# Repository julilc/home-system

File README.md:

# HOME SYSTEM

Home System is an intelligent home automation project that combines an ESP32 device, MQTT messaging, a Python backend, a SQL Server database, and a conversational AI assistant. 

The system reads environmental data such as temperature, humidity, and luminosity, stores it persistently, exposes it through a FastAPI API, and lets the user interact through a React frontend. The assistant can answer questions about the home state and invoke tools to turn lights on/off, check sensor values, and report the current status of the environment.

---

## 1. OVERVIEW

This project integrates:
* ESP32 firmware for collecting sensor data
* MQTT broker communication for telemetry and actuator commands
* Python backend with FastAPI and AI tool-calling
* SQL Server database for persistence
* React + Vite frontend for user interaction
* KiCad electrical/electronic design files for the hardware
* AI agent layer using an external model API

---

## 2. MAIN FEATURES

* SENSOR MONITORING:
  - Temperature
  - Humidity
  - Luminosity
  - Light status

* DEVICE CONTROL:
  - LED on/off commands through MQTT

* CONVERSATIONAL INTERFACE:
  - Spanish assistant named Carlitos
  - Tool-based responses for home automation tasks

* PERSISTENT MEMORY:
  - User conversations and metadata stored in SQL Server

* WEB DASHBOARD:
  - React chat interface for interaction with the home system

* HARDWARE DOCUMENTATION:
  - KiCad schematics and PCB files

---

## 3. ARCHITECTURE

The system is organized in layers. In practice:
1. The ESP32 publishes sensor values to MQTT topics.
2. A Python listener consumes those messages and persists the values in the database.
3. The backend API receives chat requests from the frontend.
4. The assistant decides whether to answer directly or call a tool.
5. Tool calls can read the database or trigger MQTT commands to control the LED.

---

## 4. TECH STACK

* BACKEND: Python, FastAPI, Paho MQTT, pyodbc, pandas, dotenv, SQL Server
* FRONTEND: React, Vite, JavaScript / JSX
* EMBEDDED / HARDWARE: ESP32, DHT11 (temp/humidity), LDR (light), MQTT protocol, Arduino C++
* AI LAYER: OpenRouter API, Chat-completions model, Tool-calling architecture
* ELECTRONICS / PCB: KiCad for schematic and PCB design

---

## 5. ENVIRONMENT CONFIGURATION

This project uses environment variables stored in a `.env` file at the project root. 

IMPORTANT:
* Do not commit real secrets or API keys.
* The repository already includes a `.gitignore` to avoid pushing `.env` files.

---

## 6. DATABASE

The project uses Microsoft SQL Server and expects a database called `home`.

SQL Scripts:
* `database_config/create_database.sql`: Creates the database
* `database_config/create_tables_and_views.sql`: Creates the tables (Temperature, Humidity, Luminosity, LightStatus, MusicPlayed, PersonsRegistered, HomeStatus, LedStatus, Memories)

Database Access:
* Connection logic is defined in: `backend/database/sql/conection.py`
* Main queries and insert helpers: `backend/database/sql/insert.py` & `backend/database/sql/select.py`

---

## 7. BACKEND & API

The backend is built with FastAPI and is defined in: `backend/api_services/api.py`

Endpoints:
* `GET /api/health`: Returns service status
* `POST /api/chat`: Receives a user message, returns an AI response (using tool calling if needed), and persists the conversation.

---

## 8. AGENT AND TOOLS

The AI assistant uses:
* `agent/planning.py`: Defines the system prompt for the assistant.
* `agent/tools.json`: Describes the tool APIs exposed to the model.
* `backend/services/agent_services/tool_registry.py`: Registers actual Python functions behind each tool name.

Available tools: 
get_temperature, get_humidity, get_luminosity, get_home_status, get_light_status, get_music_played, get_persons_registered, turn_on_light, turn_off_light, play_music.

---

## 9. MQTT LISTENER

Implemented in: `backend/services/mqtt_services/mqtt_listener.py`
It subscribes to sensor topics (Temperature, Humidity, Luminosity, LED control, LED confirmation/status) and inserts the received values into the database.

---

## 10. FRONTEND

The frontend is a React app created with Vite located in the `frontend/` directory.
It displays chat messages, sends messages to the backend, shows server/ESP32 status, and provides quick action buttons.

---

## 11. FIRMWARE & HARDWARE BEHAVIOR

Located in `firmware/main/main.ino` (and related folders).

Hardware behavior:
* Connects to WiFi and MQTT broker.
* Publishes sensor data every 10 seconds (DHT11 temp/humidity, LDR luminosity).
* Detects sound events via an interrupt.
* Subscribes to LED control messages and publishes confirmation messages back to MQTT.

Pin mapping:
* DHT11: GPIO 23
* LDR: GPIO 34
* SOUND: GPIO 26
* LED: GPIO 27

---

## 12. DOCUMENTATION & TEST FILES

* HARDWARE DESIGN: `documentation/KiCad/` includes schematics, PCB layouts, footprints, and the ESP32 symbol library.
* TEST FILES: `test/sql/insert_memories.py` demonstrates how memory records can be inserted for validation.

---

## 13. DEVELOPMENT SETUP & USAGE

1. PYTHON BACKEND: Create a virtual environment, install requirements, and run the FastAPI server via uvicorn.
2. FRONTEND: Navigate to `frontend/`, run `npm install`, then `npm run dev`.
3. MQTT LISTENER: Run the MQTT Python script to start listening to the broker.
4. FIRMWARE: Open `firmware/main/main.ino` in Arduino IDE, select the ESP32 board, configure WiFi, and upload.

USAGE EXAMPLE:
Once everything is running, open the browser and chat with the assistant.
Try prompts like:
* “¿Cuál es la temperatura actual?”
* “¿Cómo está la humedad?”
* “Enciende la luz del dormitorio”

---

NOTES:
* This is an educational/prototype system.
* It relies on a real MQTT broker and SQL Server instance.
* API credentials must be kept private in the `.env` file.

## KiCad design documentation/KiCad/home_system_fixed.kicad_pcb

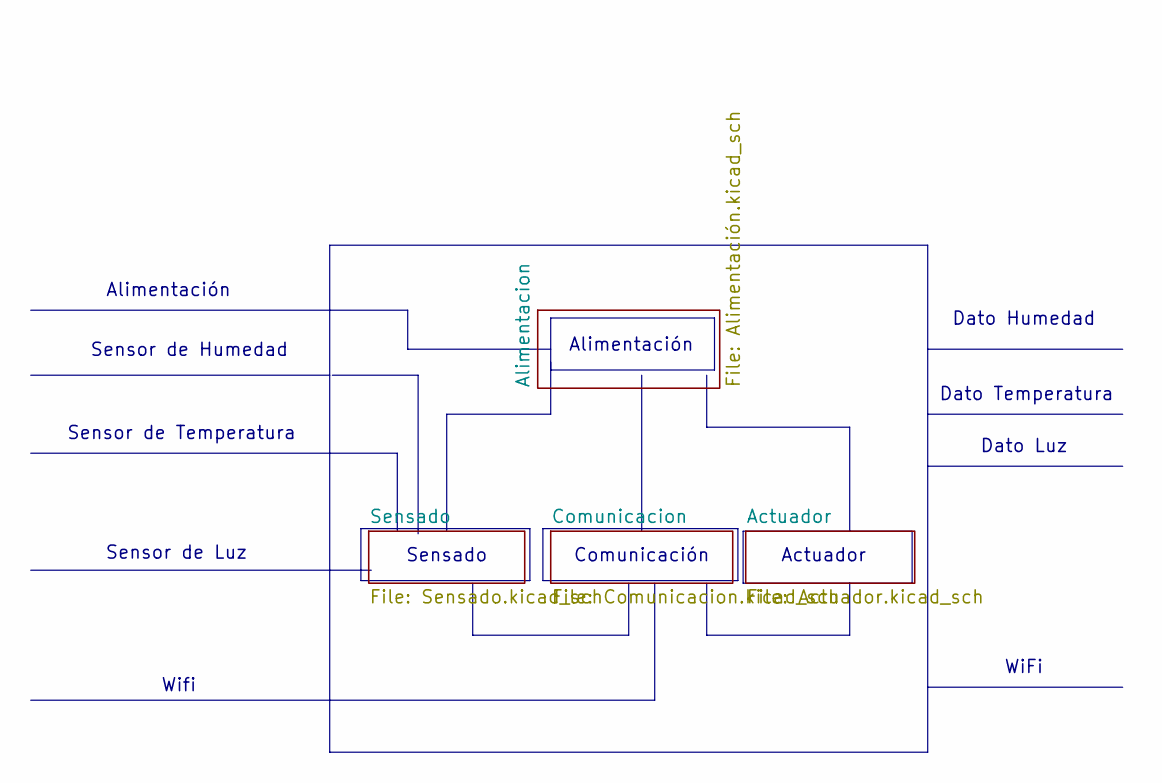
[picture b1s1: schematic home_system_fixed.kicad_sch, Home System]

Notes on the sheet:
Sensor de Humedad
Wifi
Dato Temperatura
Alimentación
Sensor de Temperatura
Dato Luz
Sensado
Dato Humedad
WiFi
Comunicación
Actuador
Sensor de Luz

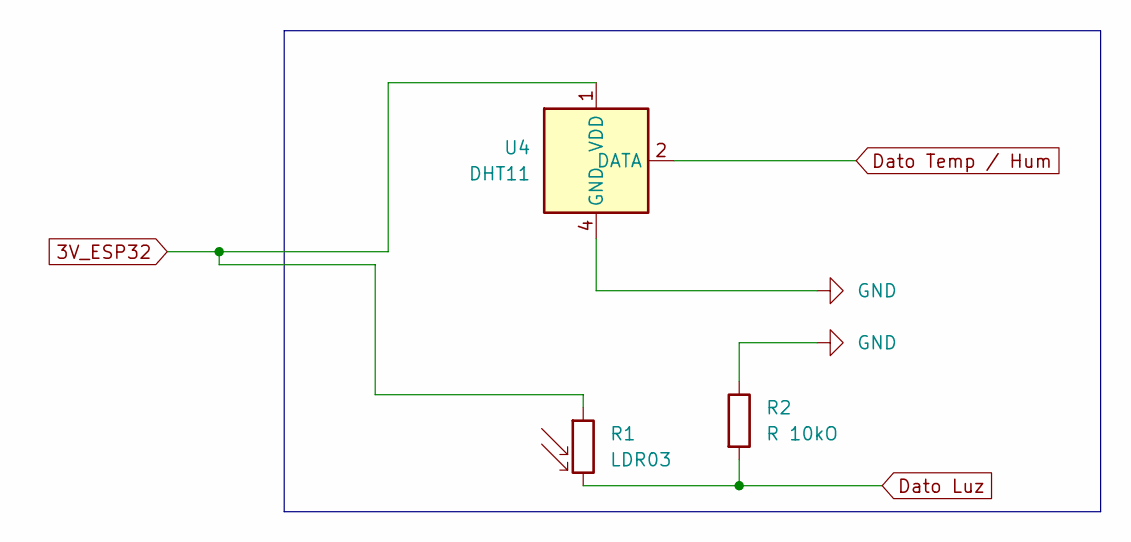
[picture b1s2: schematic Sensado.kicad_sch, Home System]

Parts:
R1: LDR03; R_LDR_10x8.5mm_P7.6mm_Vertical
R2: R 10kO; R_Axial_DIN0207_L6.3mm_D2.5mm_P10.16mm_Horizontal
U4: DHT11; Aosong_DHT11_5.5x12.0_P2.54mm

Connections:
3V_ESP32: R1.1, U4.1 (VDD); also elsewhere on the board
Dato Luz: R1.2, R2.2; also elsewhere on the board
Dato Temp / Hum: U4.2 (DATA); also elsewhere on the board
GND: R2.1, U4.4 (GND); also elsewhere on the board

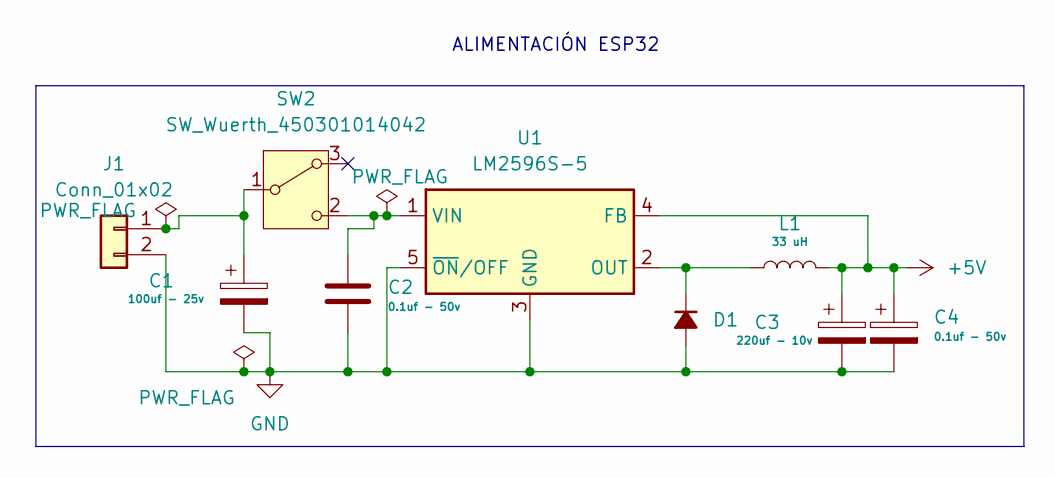
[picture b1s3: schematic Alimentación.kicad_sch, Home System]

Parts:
C1: 100uf - 25v; CP_Radial_D6.3mm_P2.50mm
C2, C4: 0.1uf - 50v; C_Disc_D5.0mm_W2.5mm_P5.00mm
C3: 220uf - 10v; CP_Radial_D6.3mm_P2.50mm
D1: D_DO-35_SOD27_P7.62mm_Horizontal
J1: Conn_01x02; TerminalBlock_Phoenix_MKDS-1,5-2-5.08_1x02_P5.08mm_Horizont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
L1: 33 uH; L_Radial_D10.0mm_P5.00mm_Fastron_07M
SW2: SW_Wuerth_450301014042; SW_Slide-03_Wuerth-WS-SLTV_10x2.5x6.4_P2.54mm
U1: LM2596S-5; TO-263-5_TabPin3

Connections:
+5V: C3.1, C4.1, L1.2, U1.4 (FB); also elsewhere on the board
GND: C1.2, C2.2, C3.2, C4.2, D1.2 (A), J1.2, U1.3 (GND), U1.5 (~ON/OFF); also elsewhere on the board
unnamed: D1.1 (K), L1.1, U1.2 (OUT)
unnamed: C1.1, J1.1, SW2.1 (B)
unnamed: C2.1, SW2.2 (C), U1.1 (VIN)

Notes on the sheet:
ALIMENTACIÓN ESP32

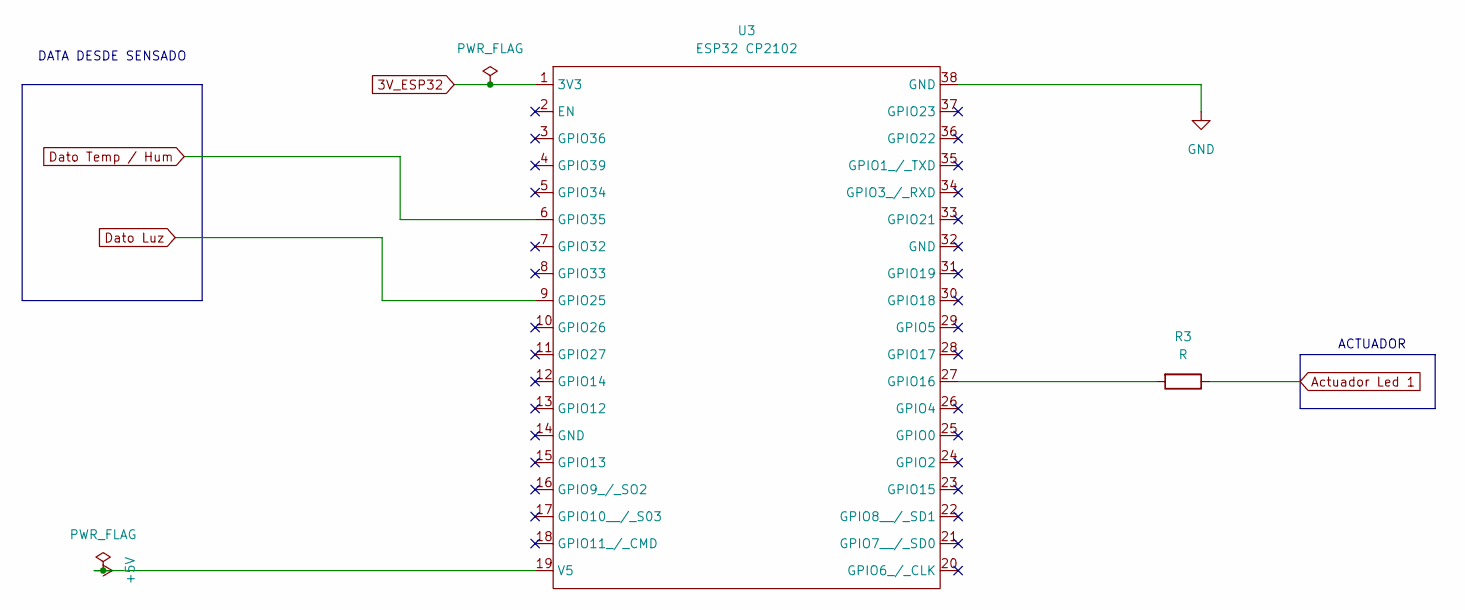
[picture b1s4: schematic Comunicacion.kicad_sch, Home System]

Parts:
R3: R; R_Axial_DIN0207_L6.3mm_D2.5mm_P10.16mm_Horizontal
U3: ESP32 CP2102; ESP32_38Pin

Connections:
3V_ESP32: U3.1 (3V3); also elsewhere on the board
+5V: U3.19 (V5); also elsewhere on the board
Actuador Led 1: R3.1; also elsewhere on the board
Dato Luz: U3.9 (GPIO25); also elsewhere on the board
Dato Temp / Hum: U3.6 (GPIO35); also elsewhere on the board
GND: U3.38 (GND); also elsewhere on the board
unnamed: R3.2, U3.27 (GPIO16)

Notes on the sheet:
ACTUADOR
DATA DESDE SENSADO

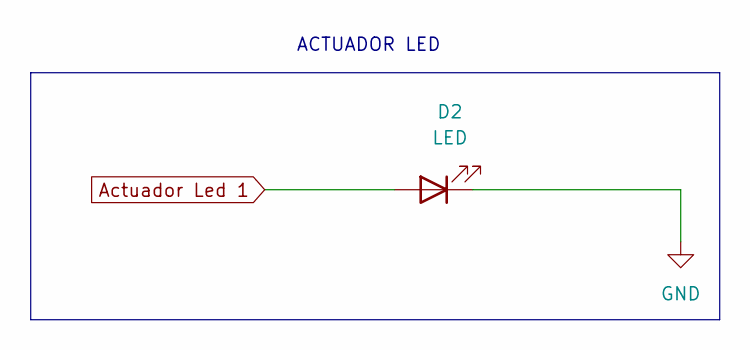
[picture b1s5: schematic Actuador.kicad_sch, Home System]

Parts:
D2: LED; LED_D5.0mm

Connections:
Actuador Led 1: D2.2 (A); also elsewhere on the board
GND: D2.1 (K); also elsewhere on the board

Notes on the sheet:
ACTUADOR LED

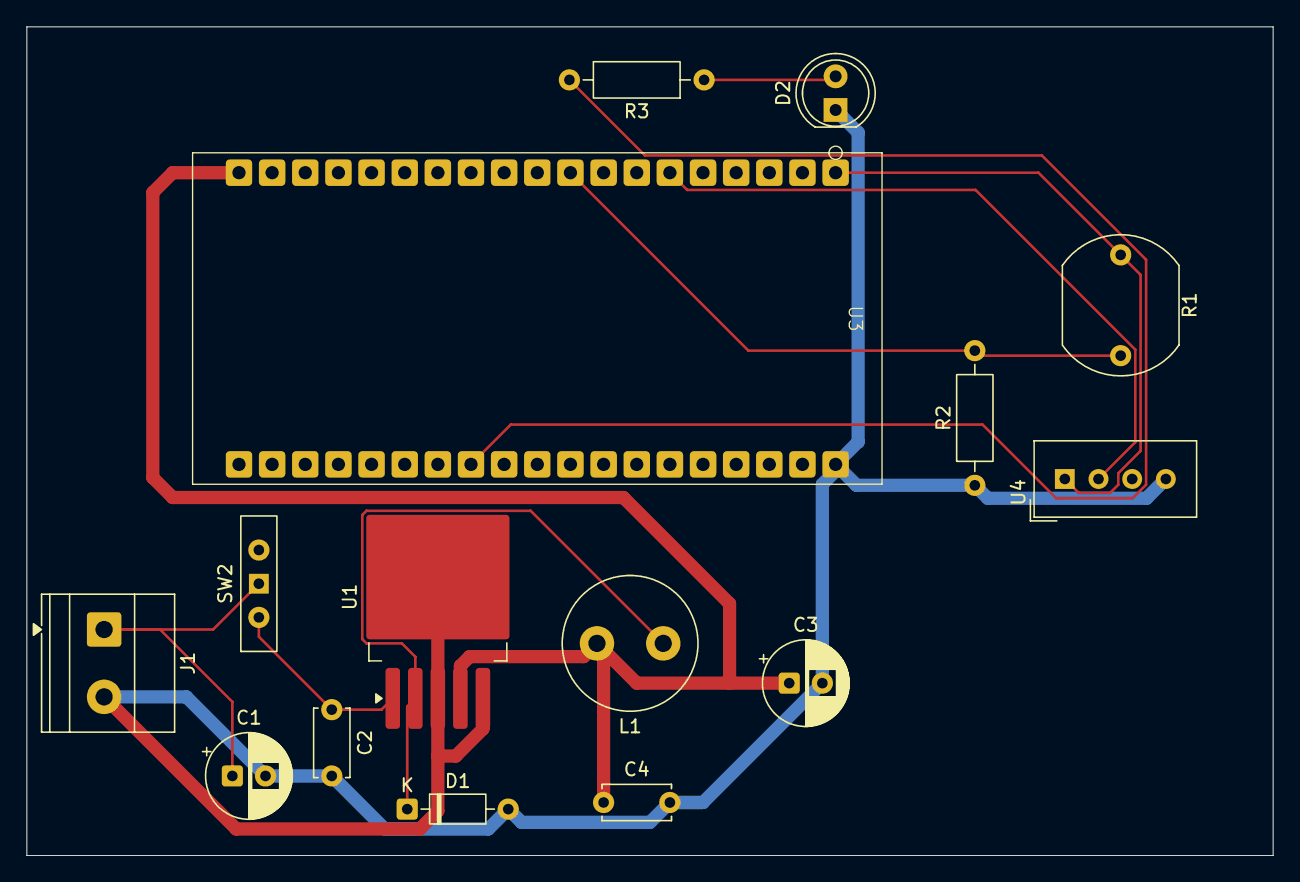
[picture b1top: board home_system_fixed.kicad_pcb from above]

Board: 2 copper layers, 94.0 x 62.5 mm, 15 parts (0 on the bottom side), 10 nets.
